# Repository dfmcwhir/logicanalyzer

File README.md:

# ISA Bus LogicAnalyzer

This is a fork of https://github.com/gusmanb/logicanalyzer. It utilizes that project's ability to chain multiple logic analyzers together with a chain of 3 of them them on a card that plugs into an 8 bit ISA bus slot. 47 of the channels are connected to A0-19, D0-7, and various other signals on the ISA bus. The 3rd logic analyzer goes to a header, so they can be jumpered over to other points on a motherboard (like buffer/latch/ram/rom CS or OE enable pins) as needed.

It is a work in progress. Circuit boards have been made and kicad and gerber files are in the electronics\ISA_Logic_analyzer folder. Assembly of the first board is in progress, so no testing has been done yet.

## About the project

This README is organized as a log of the evolution of the project and for now it will stay like this.
If you are new to the project and want to know what is this about you can start [here](https://github.com/gusmanb/logicanalyzer?tab=readme-ov-file#description)
or reading [the wiki](https://github.com/gusmanb/logicanalyzer/wiki).

Beware, the documentation is a bit outdated, I will try this summer to upgrade everything.

## Orders
- Direct order (based on availability): https://logicanalyzer.rf.gd (right now orders are not accepted)
- PCBWay order: https://www.pcbway.com/project/shareproject/LogicAnalyzer_V6_0_cc383781.html

## Enclosure
- @Bravo13 has created a pretty cool enclosure for V6.0, you can order it [here](https://www.pcbway.com/project/shareproject/Enclosure_for_LogicAnalyzer_V6_0_b82ed490.html)

## Downloads
- You can find all the compiled projects in the [Releases section](https://github.com/gusmanb/logicanalyzer/releases).
- Latest version: Release 6.0.0.1, 09/02/2025

# Beta 6.5 available

Wanna try the next version? Check [this discussion](https://github.com/gusmanb/logicanalyzer/discussions/277) :)

# ZX Spectrum analyzer by Happy Little Diodes!

If you are into retro computing and more specifically the ZX Spectrum, you should check this video by Happy Little Diodes.
He has developed an interface to connect LogicAnalyzer in a very cool way to the ZX Spectrum.

Don't miss it!

https://www.youtube.com/watch?v=IHbIW8pi4Vo

# Release 6.0 is out!

Finally Release 6.0 is completed and comes with many, many changes!

First, I have uploaded the project to PCBWay, I will still serve orders but as there is too much demand to keep up with it I also have uploaded it as a shared project, so you don't need to wait for me having stock.
The project is found here: https://www.pcbway.com/project/shareproject/LogicAnalyzer_V6_0_cc383781.html
It is right now under review so I expect it to be available in a couple of days.

Next, now the gerber files, BOMs and centroid are included in the release packages so you don't need to search inside the projects in case you want to order it from another manufacturer.

That's regarding logistics, now, a brief resume of the changes:

- Pico2 is supported, the new design solves the problems with the IO glitches.
- Total revamp of the analysis software, including speed up of the rendering, autodetection of the analyzers, and the biggest change, all the Sigrok protocol decoders are supported!
- New terminal capture application, no more long inhuman command lines, configure the capture using the terminal application and trigger the capture specifying the capture settings file! (use TerminalCapture --help for more info)
- New All-in-one package, both apps in a single zip if you want to use both!
- And many, maaaaany more changes.

Next weeks I will update the wiki with updated usage and functionalities, for now if you have doubts read the Discussion section related threads and of course if you need help feel free to open a new thread.

Have fun!

## Orders

If you are interested in buying a premade board now you can request to be added to the list in https://logicanalyzer.rf.gd/

## Orders and sponsor, what is this about?

Ok, now, the explanation. It is getting to the point of being unmanageable the amount of requests, so I have created a website to make it easier to track these, I don't want to forget anyone and doing the management manually I'm sure that in one moment or other I would forget someone...
Feel free to contact me if ytou find any problem or open a message in the discussion section.

And the sponsoring thing... I never requested anything for these projects, but lately many many people is asking about how to donate so finally I have opened a Ko-Fi account in order to accept them. Feel free to use it, anything is welcome and I will use it in improving the project whenever it is possible :)

Thanks to everyone, the support that I'm receiving with the project is amazing and I never thought that this project would rise so much interest.

### Thank you!

----

# Back!

Hi. I was in a business trip past weeks and got back today, so I have a ton of emails and messages regarding the project unanswered.

I will answer all the emails and requests this weekend/next Monday.

Sorry! :)

----

# Good news

One of the goals of the new design was to overcome the problems that the Pico 2 have. And at least, the most harmful one seems to be solved.
With the regular design the fast/complex trigger sometimes got stuck and the chaining didn't worked, with the new one the triggers seem work properly.

I need to conduct more tests as I have seen some response variations at high frequencies but I'm not sure if its caused by the pico2 itself or the transceivers as the analyzer is pushing them to its maximum limits.

I'm testing the devices with signals at 200Mhz, with the base pico all seems to work properly but with the pico2 I have seen changes on the signals, but, the TXU are rated up to 200Mhz and I'm sampling at 400Ms/s (yes, that's right, the new firmware can sample up to 400Ms/s in blast mode, I will add more info very soon as R6.0 is very close to its release 😄) so what I'm seeing is captures that have skewed samples. 
The signals that I use are basically square clocks, so I inject a 100Mhz clock what becomes two phases at 200Mhz, and with the pico2 at 400Ms/s I see that sometimes there are three samples of one phase and one sample of the other, and as far as I have seen is always the high phase the one that contains the three samples. This could be caused by the transceivers, they are at its maximum limits, but it can be also caused by the pico2, I suspect that even with the drainig of the GPIOs the signal remains high for some nanoseconds, enough to create these erroneous readings.

In any case, at least this only happens at extreme speeds and for regular use cases it should not affect the readings, and having three times more samples really expands the possibilities.

I will add more info next week after performing more extensive tests.

Stay tuned!

----

# New PCB design

I have created a new dessign for version 6.0 and is under testing right now.
It replaces the headers that were difficult to find, uses 0402 type components so is not intended for manual assembly and also include a VREF switch that allows to change between 3.3v/5v/ext vref.

Once testing is completed I will publish the dessign, I might have some spare  boards with all the components already assembled except for the pico, so if you are interested in one of these leave a message un the discussion sections (if I see that there is enough demand I might even think on making a batch of these).

----

# Pico 2: born dead.

Ok, this are bad news. The Pico 2 has been released in a basically useless status. It has been detected a bug in the GPIO hardware that locks the pins whenever you input a high level, what is known as "Errata E9".
According to the official errata the lock only happens when the pull downs are enabled, you input a high level value and then the GPIO starts outputing 2.1v. That doesn't sounds too bad but the reality is very different. I've been testing it and even forcing the pulldowns to be disabled, the PIO triggers the lock.
In this state, the RP2350 is useless if you need to use the GPIO's to input any data. The only workaround provided is to disable the pins and enable them when you are going to read and disable them after it to reset the pin status, but as you can imagine with the PIO this is impossible, and even if it was possible the capture speed would be reduced so much that the analyzer would be totally useless.

Unfortunatelly I must stop the port to the Pico 2 until this situation is solved.

# Pico 2: a game changer?

I've started checking the Pico 2 and porting the code to it. I must say that it has been one of the easiest transitions that I ever did, just reconfigure the cmake scripts, change a couple of lines, and voi-la! the project runs in the pico 2.

This is the base code, no changes at all, but from here I have multiple improvements to do, starting with the DMA (no mode ping-pong DMAs for the Pico 2, a single DMA can do all the work simplifying the code A LOT) and then upgrading the buffers to three times what are now, I expect to have up to 380k samples :)

Said that, I started checking the limits of the pico 2 and... well, I'm really surprised, with the original pico I only got stable up to 200Mhz, beyond that I had problems with the flash and it got hung, but, oh my gosh, this thing (the pico 2) right now is running at 400Mhz without a single hicup!!

Of course I had to raise the voltage to 1.4v for the core and it gets warmer, but I added a little heatsink to it and it's perfectly fine. Soooo.... I need to test this in deep but this may be a very, very big change, not only three times the samples than the pico, but also twice the speed!

Stay tuned for more news!

----

# Help wanted!

I'm cooking something very special, if you whant to know what it is and help with it, [check this post](https://github.com/gusmanb/logicanalyzer/discussions/127).
😉

# More boards on the go!

One of the new functionalities of the RP2350 is the capability of having two XIP devices and also has the full device implementation (RP2040 only had READ capabilities implemented). This means that is possible to have (for example) a flash device *and* a PSRAM connected to it.
Unfortunatelly the Pico 2 does not expose the QSPI pins and they are tied directly to the flash... But there is hope! PiMoroni has developed the PiMoroni Pico Plus 2 which contains 16Mb of flash and 8Mb of PSRAM.

I already have ordered one of these new boards and have some ideas on what could be done with them :D
Right now the most possible one is this: PSRAM is not fast enough for sampling at a decent speed with many channels, BUT, it is fast enough for something like storing ADC samples, so what I'm going to try is to allow the mix of analog and digital channels. The analog channels will be very slow compared to the digital ones (only 500Ks/s) but it still can be useful to monitor behaviors of things like motors, servos or whatever. As the PSRAM is 8Mb it will allow to store up to 8 seconds of analog data on single channel mode (2 bytes per sample at 500Ks/s is roughly 1Mb/s of data), this, combined with the upgraded onboard ram and the burst mode can be really useful in multiple projects.

Stay tuned for more news!

----

# Exciting news! The Pico 2 is coming soon!

As some of you may know the Pico 2 is being released this month. The new Pico 2 is a very exciting upgrade of the pico, more powerful cores, two alternative RiscV cores, three PIO units instead of two and 520Kb of RAM!

This can be a game changer for LogicAnalyzer, only with the new ammount of RAM the quantity of samples is going to increase massively, we're talking about three times the current ammount of samples!

Also, there are really exciting changes on the PIO side, the new IRQ system allows to intercomunicate the PIO units, this means that the trigger pins could be freed now, and this, as small change as it seems can be really amazing combined with the new third PIO unit... Think about this, a 64Mb dual SPI RAM running at 100Mhz connected to the two free pins and controlled at full speed by the third PIO unit... 

I was preparing a release for this month but it's going to be delayed, once I receive the new Pico's I will start the development for the Pico 2 and once it's completed I will release all at once.

Stay tuned!

## RELEASE 5.1

This release is a QoL release with some functional corrections. For more details check the release page.

## RELEASE 5.0, Burst mode is here!

New release with exciting feature!

The biggest change on this release is the Burst mode. With burst mode you can capture blocks of data and the analyzer will rearm itself immediatelly and capture more data when the trigger condition is met again. This will improve the memory usage discarding unneeded samples! Right now only the simple trigger mode accepts burst mode but in a future I will try to implement it in all the other triggers.
For more information check [the wiki.](https://github.com/gusmanb/logicanalyzer/wiki/06---The-LogicAnalyzer-program#triggers)

Also new features to ease the navigation in the capture viewer have been added like shortcuts and a preview of the full capture. More info in [the wiki.](https://github.com/gusmanb/logicanalyzer/wiki/06---The-LogicAnalyzer-program#navigating-on-the-capture-viewer)

Finally multiple improvements have been done, some bugs in the capture tail detection have been corrected, the USB transfer has been improved using directly the CDC transfer functions and more.

Beware that this version is not compatible with other ones, the protocol has changed. The driver will check the device version and will not connect to it if it is lower than V5.0.

Have fun!

----

## UPDATE 28/06/2023 - Release 4.5.1 - QOL improvements

This release include some QOL updates to the applications.

LogicAnalyzer app:

* Ammount of on-screen samples will be preserved if you repeat the last capture.
* Added a new menu entry called "Repeat las analysis" to the protocol analyzers, it will execute the last analysis performed to speed up things.
* Changed where config files are stored, they will use the %appData% folder now ($home/.config in Linux).
* Changed horizontal scrollbar visibility.

CLCapture app:

* Now channel names can be provided from the command line.

Have fun!

----

## UPDATE 11/04/2023 - Release 4.5 - Support for the RP2040-Zero and new board definition system

This release includes only an update to the firmware.

First, the RP2040-Zero is now officially supported (no shifter board for it though). 
You can download the firmware for it on the [releases](https://github.com/gusmanb/logicanalyzer/releases) section. Also, the pinout has been added to the [wiki](https://github.com/gusmanb/logicanalyzer/wiki/02---LogicAnalyzer-Hardware#barebones-configuration) so you can use it with the bare-bones configuration.

And second, the firmware has been refactored in order to make a lot easier to add new boards. You have the complete instructions on how to add support to a new board on [the wiki firmware section](https://github.com/gusmanb/logicanalyzer/wiki/03---LogicAnalyzer-Firmware). Also, as some boards include the very popular WS2812 RGB led the firmware includes a driver for it, it's purely software-based, no timers nor interrupts needed, so feel free to use it if you want.

If you add support for a new board, feel free to create a pull request with the changes :)

Have fun!

----

## UPDATE 25/02/2023 - Release 4.0 is up! Channels a go-go!

Hi again! This is a BIG update loaded with new functions and improvements to the hardware, firmware and software!

Let's start with the little things: we have a logo! Yes, it's nothing important but I hated to not to have a proper one so I designed one that I think fits well to the project :D

Next, we have a proper Wiki! All the project has been documented: hardware, firmware and software. If you have any doubt check it as I have tried to explain everything related to the analyzer usage in there. If you find any error or missing feature please open an issue and I will correct it as soon as I can.

Ok, now the changes to the hardware. There is a new pcb for the analyzer that includes two connectors to daisy chain the analyzers. You can use two or three Dupont wires (the central pin is unused, it's reserved for future usage, I have left it there so anyone that produces these PCB's can patch them easily).

And the firmware has also been updated to support the daisy chaining. So, what is for the daisy chaining? Well, daisy chaining allows to chain up to five analyzers without wasting pins so you now will be able to capture a massive ammount of **120 CHANNELS!!!** Check the [Connection](https://github.com/gusmanb/logicanalyzer/wiki/06---The-LogicAnalyzer-program#connecting-to-devices) and [Capture](https://github.com/gusmanb/logicanalyzer/wiki/06---The-LogicAnalyzer-program#capture) sections of the Wiki to know all the possibilities and how to use them.

Now, the software. It contains many changes, so I'm going to start with the improvements and then with the new functionalities.

First I have improved the sample rendering. It is now more visible and looks a lot better. Also, the guides shown to see where a sample starts and ends are automatically scaled or removed, it made no sense to have so many lines that they made a solid gray background, so when there are too many they will get automatically deactivated. Also, this allowed to improve the performance so now the sample viewer will allow to show up to 2000 samples in screen without any check.

Related to this the protocol analyzer renderer has been updated, it will take less useless space and will hide the information if it does not fit in the assigned space.

Now, the connection system has been updated to include a "multidevice", this is the device that you must use when using the daisy chained analyzers.

Next, the capture dialog has been updated, the mode selector has been removed and the mode is autoselected based in the channels enabled, check the [Wiki page](https://github.com/gusmanb/logicanalyzer/wiki/06---The-LogicAnalyzer-program#basic-parameters) to know the limits and modes.

Also, the capture dialog has a new channel selector, more visual and that includes the name field for the channels, instead of configuring the names after the capture has been finished (and lose these if you capture again) the names can be entered directly on the capture dialog. These names will be preserved between captures (and if you change them from the channel viewer these changes will be respected).

This new channel selector also allows to show up to the 120 channels that can be used when daisy chaining five devices, the selector will have a scrollbar when the channel list is bigger than its space.

Another change, the editing features have been improved and expanded. First of all, you will not need to create regions to execute edit actions, the sample range selection has been improved and it is used now for these. Check the [Wiki page](https://github.com/gusmanb/logicanalyzer/wiki/06---The-LogicAnalyzer-program#editing-captures) to see a description on how it works and which new features have been included.

Finally, the system now can create capture files from scratch, for this I have implemented a language that allows to describe signals in an easy way, it even includes a colored syntax editor, check the [Wiki](https://github.com/gusmanb/logicanalyzer/wiki/06---The-LogicAnalyzer-program#the-signal-description-language) for a description of this language!

Also, I already have planned the next update, I'm not sure when it will be ready but I will implement it for sure, and this is one of the motivations to create the SDL language: replay captures! ;)

This is a resume of the most prominent changes, surely that I forgot some, but all are documented in the Wiki, so ensure to review it!

Any feedback about the update will be welcome, so don't hesitate to open issues or start discussions.

Have fun!

## UPDATE 07/02/2023 - New release with updated shared driver.

This is a bug-fix release, with the introduction of the Pico-W WiFi support I unified the transfer mode in the driver using streams for network and for the serial port, but I forgot that .net 6.0 Ports package causes problems with Linux, so the previous release will hung the app when receiving more than 4k samples... Doh!

I have updated the code to use the same work around that I used previously and the problem has been fixed.

Have fun!

----

## UPDATE 04/02/2023 - New release! Bugs corrected and more samples!

Hi! This update comes loaded of news.

### First of all, bug corrections. 

The biggest bug that has been corrected is the fast trigger in the Pico-W. When I implemented the Pico-W I tried it extensively, but I used only the simple trigger to do the tests. What was my surprise when I tried to use the Pico-W with a fast trigger and I found that it got completely hung!

The thing is that the Pico-W hides a little secret that I haven't found documented anywhere, this little secret is that the driver uses a PIO program to do the transfers! The fast trigger uses a full PIO unit, all its 32 instructions to create a jump table, and the CYW driver uses a SM in the PIO1 to do the SPI transfers. So I tried to swap the PIO units and it at least started to capture, but the capture was never finished, I have revised up-to-down the driver and still haven't found why the PIO1 interrupts don't work at all after the CYW driver has been enabled, so I have done a work-around that does not need the IRQ to trigger a handler. So, if you are using a Pico-W update the firmware asap.

The next bug is a small bug that caused that some samples weren't clear correctly when a trigger was rised immediately after starting capture (for example the trigger condition is already met when the first sample is done).

### And now, the really big news, MORE SAMPLES!

I have tweaked the buffer transference between the PIO and the memory and it allows to hold up to 131071 samples! Of course this is at the expense of how many channels you use, the device now has three modes: 8 channels, 16 channels and 24 channels.

The sample limits are specified here:

 * Mode 8:
 
     * Minimum pre-samples: 2
     * Maximum pre-samples: 98303
     * Minimum post-samples: 512
     * Maximum post-samples: 131069
     * Maximum total samples: 131071
     
 * Mode 16:
 
     * Minimum pre-samples: 2
     * Maximum pre-samples: 49151
     * Minimum post-samples: 512
     * Maximum post-samples: 65533
     * Maximum total samples: 65535
     
 * Mode 24:
 
     * Minimum pre-samples: 2
     * Maximum pre-samples: 24576
     * Minimum post-samples: 512
     * Maximum post-samples: 32765
     * Maximum total samples: 32767

As you can see, using the 8 channel mode you can capture up to four times the samples that were available until now, a substantial increase.
The channels used for 8 and 16 modes must be the first ones, you cannot choose eight random channels, and this introduces a limitation, they collide with the complex and fast triggers (not the simple trigger, for that you still can use any channel left). Bear in mind this to plan how you configure your capture, for example for the 8 channel mode you still can have a 8 channel complex trigger or a fast 5 channel trigger without including these channels in the capture, but if you need more channels for one of these triggers, or you need to use the 16 channel mode you will suffer of this.

### Another new update, now you can show up to 1024 samples in screen!

You can activate this feature from the main screen, it has a checkbox (which will warn you as this may be a very CPU intensive task for old computers) that allows you to change the on-screen samples from 200 to 1024, this is really useful for use with big screens and modern computers.

Also I have tweaked a bit the appearance of the sample viewer, I didn't liked the dashed lines so now all are continuous ones.

Well, that's it for now.

Have fun!

----

## UPDATE 03/02/2023 - Measurement tool.

This is a very handy update to the analyzer, you can measure a region and get information of each channel: total samples selected, period of the selection, number of positive pulses, number of negative pulses, average and predominant period for positive and negative pulses and average and predominant frequency.

The predominant values are calculated applying a variant of the 95th percentile rule to discard aberrant/broken samples and I must say it works really well, it matched exactly all the frecuencies I have tested.

There is still no new release, you will need to compile the application if you want it, but I will create the release very soon.

Have fun!

----

## UPDATE 02/02/2023 - I2C protocol analyzer.

New day, new analyzer :D. This time is the turn for I2C. The analyzer will show you the raw data, the ACK/NACK's and will also show the device address (7 and 10 bit modes), operation of a request and any kind of frame error. To install it get it from [here](https://github.com/gusmanb/logicanalyzer/blob/master/I2CProtocolAnalyzer.dll) and copy it to the "analyzers" folder of the application.

Have fun!

----

## UPDATE 01/02/2023 - Serial protocol analyzer.

This is a small update, I have created a serial protocol analyzer (RS-232). This update does not include a release but I have left the analyzer library compiled in the repository. To install it get it from [here](https://github.com/gusmanb/logicanalyzer/blob/master/SerialProtocolAnalyzer.dll) and copy it to the "analyzers" folder of the application.

It supports positive and negative polarity (for TTL and RS-232 level signals), two channels (RX + TX), 7 or 8 bits, no parity/odd parity/even parity and 1, 1.5 or 2 stop bits.

Have fun!

----

## UPDATE 31/01/2023 - Pico-W support and WiFi!

It's finally here! WiFi support!

First of all, there are now three different firmware versions in the release section, one with no suffix for the regular pico, another with the "W" suffix for the Pico-W with no WiFi support and a final one with the "WIFI" suffix for the Pico-W with WiFi support. Choose the one that best suits your needs.

Now, how to use the WiFi support?

First of all, you need a Pico-W, I think that's obvious :D, flash it with the "WIFI" firmware and the device is ready to be used. If you plan to solder the Pico-W to the analyzer board beware to not to add the debug pins as they are now located in the middle of the board and it will not allow you to solder it, if you want them then you will need to use some pin headers to rise the Pico from the board (for my own device is what I always have done, in this way I can replace the Pico whenever I want).

Ok, now let's see how to use it.

First of all, you need to connect at least once the Pico-W to the computer to configure the network settings, this process can be done as many times as you want, connect the Pico-W to the computer and use the CLCapture or the LogicAnalyzer software to configure it.

When you connect the Pico-W with the WiFi firmware you will notice that a new menu gets enabled:

From there you can then select the "Update Network Settings" menu.

That will open the dialog to configure the network settings, you must enter the SSID of your router, the password (only WPA2 is supported), the desired static IP address and the listening TCP port.

Once these are configured accept them and they will be saved to the Pico-W flash, immediately the Pico-W will try to connect to your router, if it's available it will connect and it will be available for network connection.

To connect to the Pico-W through WiFi you must select from the dropdown menu the "Network" option.

Once you select it and press the "Open" button the network connection dialog will open.

Fill the IP address and port and press "Accept", if the device is available it will connect to it.

And that's it! From that point the device works exactly as before, for the application is indifferent if it is connected through network or USB, it has the exact same functionalities.

### The CLCapture updates

The CLCapture also supports the network connection and configuration, for that purpose now the command line starts with a verb, execute the program without any parameter to check the verbs and only with a verb to get the required parameters.

### Some notes

Both interfaces (USB and WiFi) work at the same time, but when a client gets connected through WiFi the USB will be ignored until the client gets disconnected, keep it in mind.

I have found some quirks on the Pico-W WiFi support, the first one is that it does not support at all to connect without a DHCP server, and it always gets the network information from there, fortunatelly I have found a way to change the IP address once it is connected to the AP. This also causes a problem (at least in my router), if you are already connected to the AP and you change the network settings the device disconnects from it and reconnects with the new info, if is the same AP (per example you have just changed the IP address) the static IP is ignored and it will retain the one assigned by the DHCP server, the solution is easy, restart the Pico-W and it will connect with the new IP address.

The firmware now has three "flavours" when compiled, this is controlled from the "LogicAnalyzer_Build_Settings.h" header and the "CMakeLists.txt" files, both contain instructions on how to change the settings based on your preferences.

A user adviced me that the Pico-W may have problems if the USB is connected to a host and the WiFi is used. I haven't experienced none of these and I have tested it extensively, maybe as I have used a sepparated core for the WiFi it avoids this kind of trouble, but if you experience them then use a USB power supply (like a phone charger or similar) if you want to connect through WiFi.

### The future

I'm thinking about creating a new PCB board that contains a battery and an USB charging module, in this way the device will become totally free of wires (except for the ones for the signals, obviously). I think this could be extremely useful, you will be able to place the analyzer even inside a computer or any kind of device and connect to it remotely, I think this could be extremely useful for devices that are in fixed places or are big and difficult to move (like old mini computers or car ECU's).

Stay tunned for more news, and be sure the project still is not completed!

Have fun!

----

## UPDATE 29/01/2023 - Software update

This release contains many updates to the GUI, CLI and driver and also includes many new target architectures.

### Updates to the GUI

First, the sample viewer and sample marker contains also the half of the cycle (where the sample was done in the cycle) to make it easier to see the data.

Now you can create a "user mark", it is a temporary mark and is not saved with the save/export data, just an useful tool to see things. Click on the sample marker without dragging and you will set the user mark place. To remove the user mark click again in the same spot.

Deleting samples is now possible, when you right-click on the sample marker over an existing region now instead of deleting the region it will pop a menu which will allow you to delete the regions that were under the mouse or to delete the regions *and* the samples.

Added more meaningful error messages, in any case the limits in the numeric up/down controls have been updated to match what the driver expects.

### Updates to the CLI

It also includes the new messages with more meaningful errors.

### Updates to the driver

The driver has been adjusted to give more flexibility in the pre/post samples, the valid parameters now are:

    -Frequency must be between 3.1Khz and 100Mhz
    -PreSamples must be between 2 and 31743
    -PostSamples must be between 512 and 32767
    -Total samples cannot exceed 32767
    
Have fun!

----

## UPDATE 17/12/2022 - Application repackaging

One of the features that I loved for .net when it was introduced is the ability to create applications that does not require the user to install the .net Framework independently. I always prefer to create portable packages, something that you uncompress wherever you want and it just works. This creates a bit bigger applications but nowadays with the massive storage devices we have and the fast Internet we have this is not a problem, while having to install the framework can be painful in some cases (restricted user privileges environments, problems with old .net installations, etc).

Well, thanks to the people at [Laboratoire Ouvert Grenoblois](https://www.logre.eu/) I found that the packages for unix/macos where incorrectly packaged and didn't included the framework and needed its installation... Doh!

I have re-packaged all the applications (CLI and GUI) and now all the versions include the required files, it should not need any more the installation of the .net framework.

Also, I have bumped up the firmware to the version that includes the new tail detection (beware, it will still inform that is the V1.0, I will correct the version numbering with the release of the Pico-W support).

Note: If you already have the applications and they are working ok for you that means that you already have the framework installed and there is no need to download the new packages, you only need these if you're doing a new installation or you had problems with the previous versions because the missing framework.

Have fun!

----

## UPDATE 12/12/2022 - Working towards Pico-W support

One of the goals that I want to achieve with the analyzer is to support the Pico-W. Would not be great to have a battery powered analyzer that connects to your computer via WiFi? For me at least this is a really desirable option as I have my main computer on a different desktop than the electronics bench, so when I want to analyze signals I must have a long USB cable hanging from the computer to the analyzer or I must do the analysis in the computer desktop. Also even if you are in the same desktop the less cables that you have around the easier is to work. For this, the Pico-W is ideal, as the analyzer does not transfer data in real time it does not need an extremely fast connection, for transferring the data once it has been captured the integrated WiFi of the Pico-W is more than enough.

### Pico-W missconceptions

It has been a while since I got the Pico-W and I didn't had enough time to start really digging on how the thing works, so my previous knowledge about the W was based on the first notes that were released to the Internet (I bought it at release day). Something that was stated in many places was that the W used some GPIO's to control the WiFi module so you would have less available IO's for your usage.

I have been really pleased when I have read by myself the datasheet and how the Pico has implemented in reality the WiFi module. It indeed uses some GPIO's to control the WiFi, but, those GPIO's have never been available to the user as regular GPIO's. The Pico uses GPIOs 23, 24, 25 and 29 for internal usage (LED, VBUS sense, etc). So, what have they done in the Pico-W to not to use additional GPIO's? They have lifted those functions to the GPIO's of the WiFi module. The WiFi module itself contains a GPIO port and now that port is the one that contains those functionalities, so now GPIO's 23, 24, 25 and 29 control the WiFi module and the first three GPIO's of the module are used for those functions.

So, what does all this means for the analyzer? Well, it means that very little changes needs to be done in the capture code and only the front-end code needs to be changed. Also, this means that the W version will also retain all the 24 channels, it will not lose any capability. Wohooo!!!

### Changes to the capture code

As all the GPIO's that are used to capture are the same there is no need to change any code except for one very small part, the "end capture" mark. The PIO always capture pins in a sequential way, it means that you cannot have "holes" in the pin sequence, and to get the full 24 channels every single available GPIO must be used, up to GPIO28. This means that the GPIOs that controlled the LED's, VBUS and so on also are captured but ignored. Said that, to mark where the capture was finished in the buffer a special value that was impossible to happen was added after the last capture, it was based on that the device those GPIOs would never be 1's. In theory, as we are capturing 32 bit words there will always be some zeroes at the tail, but I'm paranoid and also it is not elegant, so I decided to modify the tail detection code.

Instead of basing the tail detection in a mark in the buffer (which requires to iterate the buffer until it is found) now the tail detection is based in the DMA channels transfer state. This was my original idea, but unfortunatelly the Pico API does not expose a direct way of reading how many transfers have been done or how many are left, you can set them but cannot read them, so I abandoned that idea.

This time I have digged a bit more and went directly to the RP2040 datasheet and it states very clear that the TRANSFER register is R/W, so you can read how many transfers are left. I have no idea why the API does not expose it, but knowing that is very easy to access directly to the register using the dma hardware channel structure.

Now what the code does is: once the capture has finished before aborting the DMA channels it checks which one is busy (remember, there are four DMA channels in a ringed chain, so only one DMA will be busy, the one that's waiting for the next transfer from the PIO), checks how many transfers are left and based on the DMA channel number and the transfers left it computes the index of the last capture.

This is more elegant, faster and prevents that my paranoid side rings a bell each time I see that code thinking on the Pico-W, so all are advantages :D

### Wanna try it?

In the repo source under the [build](https://github.com/gusmanb/logicanalyzer/tree/master/Firmware/LogicAnalyzer/build) folder you will find the UF2 file with the new detection code, so you can try it with the Pico-W, it will still use the USB to transfer the data but you can check its compatibility. I still haven't got time to try it in the W but I plan to do it soon. In any case, if you test the new firmware in a W or a regular Pico I would be thankful if you can leave a comment telling your experience, if you have found any problem or if it worked as expected.

### Next steps

Well, the next step will be to add the front-end code for the W, the idea is to have a single project that based on settings compile it for the W or for the regular pico. About how to implement it, I still need to check the W API for the WiFi, but one thing that I want to do for sure is to have the WiFi module off when the capture is running to avoid any kind of glitch because interferences, I fear that the traces may act as antenna and read false data, so I'm thinking that I will use UDP instead of TCP, use a broadcast address to send/receive data and as UDP does not require an stablished connection it will allow to shut down the module without breaking the network. In any case these are my first thoughts and may change once I start implementing it.

Have fun as always!

----

## UPDATE 27/11/2022 - Small changes, great value

I have uploaded a new version of the PCB's and the firmware. It contains a small modification which can give great value to the device.
Do you have an oscilloscope? Have you ever wanted to trigger it based on the value of a data bus? Or when some digital signals take a concrete value?
Now the logic analyzer offers this functionality!

The modification is very simple, the GPIO pins used for the complex/fast triggers have been exposed through a diode and that signal can be used to trigger other devices like an oscilloscope. Or even you can chain multiple logic analyzers to have as many channels as you want! Configure your analyzer for a complex or fast trigger, connect your device to one of the EXT pins (and GND as needed) and start the capture. To chain multiple analyzers you must configure a simple trigger and connect one of the pins on the secondary analyzers to the EXT trigger pin. In the future and if it is requested I will add another capture mode for the EXT so it can chain more than 3 analyzers.

There is a small delay from the trigger to the signal, I have measured it and it is a delay of 20ns for the fast trigger (the two cycles that takes to detect and propagate the trigger condition) and 35ns for the complex one. Also, the diode introduces a small delay of 4ns, if you want to remove that delay you can skip the diode and the pull-down resistor and place a bridge where the diode should be placed, but be ware that you will leave the trigger unprotected against polarity inversions.

The external trigger has been routed to two pins, in this way you can chain as many analyzers as you want, or connect two other devices.

The new pinout is this:

Beware to not to use a new analyzer with an old shifter board, it has been also modified to include the ext signals, if you use an old sshifter with a new board you will create a short between +v5, +3.3v, GPIO0 and GPIO1 what will be fatal.

For the new shifter the pinout is the same as the analyzer but the +5v pin is the +5v/ext_ref depending on the jumper setting.

Finally I also have updated the firmware to disable the GPIO synchronizers what reduces other 4ns of delay.

Have fun!

----

## UPDATE 03/09/2022 - Abort captures
Minor release adding the capability to abort a running capture. To use this feature you will need to update the firmware and the application.

----
## UPDATE 27/08/2022 - LevelShifter update and more...

I have updated the level shifter board. It's a minor change but it makes the shifter a lot more flexible as now you can use the internal +5V as reference for the input voltages or you can use an external voltage source as reference. Basically this allows you to use the target device's voltage sources as VRef so the board now can work with levels between 1.65v and 5.5v

New board:

To use an external VRef source you need to remove the jumper JP1 and connect the external voltage reference to the +5v/ExtVRef pins of the input header.

BEWARE!!! There is no overvoltage protection for the VRef input so you must be careful to respect the 5.5v maximum voltage limit.

#### More things to come very soon:

- Capability to abort a running capture (under testing)
- Enclosure for the analyzer (a preview is already in the repository, do not use as I'm on the process of adjusting it)

Enjoy it!

----
## UPDATE 31/07/2022 - RELEASE 2.0

Good news! The multiplatform application is ready!

The application has been completely rewritten using AvaloniaUI, it works in Windows, Linux, Linux-ARM (Raspberry) and MacOSX.
It has been tested under Debian, Raspbian and Windows 10, MacOSX has not been tested as I don't have a working mac but it should work without problems.

Also, the new app includes improvements over the original one, like the ability to export the captures to Sigrok and better performance in general.

Application running in Windows:

Application running in Linux:

Application running in Raspberry:

----
## UPDATE 13/07/2022

I have managed to finally test the command line application in Linux and it worked as expected so I'm releasing it.

The command line capture program is a multiplatform command line application, it has versions for Linux, MacOSX and Windows and allows to capture data directly to a CSV file. The file format is compatible with Sigrok/PulseView so you can analyze the captures with it.

NOTE FOR LINUX/MACOSX USERS: Due to how I compile the apps you will need to make the app executable with CHMOD.

The app has been tested in Linux and Windows, if any user tests it on MacOSX please leave an issue with the results, I will be very thankful :D

### How to use the command line app:

If at any moment you need help you can execute `./CLCapture --help` and it will show you the usage help.

The app requires seven parameters to start a capture: serial port, sampling speed, channels to capture, pre-trigger samples, post-trigger samples, trigger definition and output file name.

- The first parameter is the name of the serial port of the logic analyzer.
- The second parameter is the desired capture speed in samples per second.
- The third parameter is a list of channels separated by coma, per example `1,2,3,4` or `1,16,24`.
- The fourth parameter is the number of samples to capture before the trigger.
- The fifth parameter is the number of samples to capture after the trigger.
- The sixth parameter is the trigger definition expressed in the form of: "TriggerType:(Edge, Fast or Complex),Channel:(base trigger channel),Value:(string - containing 1's and 0's indicating each trigger chanel state)". Per example, if we want an edge trigger on the positive edge using channel 4 the value would be `TriggerType:Edge,Channel:4,Value:1`. If we would want a fast trigger using channels 3,4,5 and a pattern of "101" the trigger definition would be `TriggerType:Fast,Channel:3,Value:101`. Note that there are no spaces, each parameter is separated by coma and no quote is used.
- Finally the seventh parameter is the output file name we want to generate.

A complete example to capture channels 1, 2, 3 and 4 at 100Mhz using channel 5 as positive edge trigger and storing the results in a file called "output.csv" would be similar to this:

```./CLCapture /dev/ttyACM0 100000000 1,2,3,4 512 1024 TriggerType:Edge,Channel:5,Value:1 output.csv```

If everything goes Ok you will see something like this:

```
Opening logic analyzer in port /dev/ttyACM0...
Conneced to device LOGIC_ANALYZER_V1_0 in port /dev/ttyACM0
Starting edge triggered capture...
Capture running...
```

The analyzer will blink while the capture is running and once it has finished it will print the result:
```
Capture complete, writting output file...
Done.
```

This capture will contain the data in CSV and is compatible with PulseView. To import it in PulseView go to "Open->Import comma-separated values...". The file is generated in a way that you don't need to change any of the CSV paramters, you will need to specify only the number of channels and the capture speed.

Once imported you will see your data, something like this:

I hope that with this, at least until the multiplatform app is ready, all the users can use the analyzer the way they want, it will work in all the common OS'es and it introduces compatibility with Sigrok/Pulseview in a way that is not intrusive for Sigrok nor for the LogicAnalyzer app.

Have fun!

----
## UPDATE 12/07/2022

I have received the shifter PCB's and there is an error. The footprints of J1 and J2 are exchanged, so what should be inputs are outputs and vice-versa. Thankfully this is not a problem, as the PCB is completely symmetric and it has components in both sides flipping the board fixes the problem.

Board before flip.

Board after flip.

The KiCad project is already updated.

The good news is that the board works like a charm, I have tested it with my clock generator with a 50Mhz clock and it captures every single half cycle perfectly, like if the board was not there :D

So if you want to build your own shifter board, it's ready and tested.

----
## Description
Cheap 24 channel logic analyzer with 100Msps, 32k samples deep, edge triggers and pattern triggers.

----
## Overview
LogicAnalyzer is a very cheap analyzer based in a Raspberry Pico. The analyzer offers up to 24 digital channels, pre and post trigger sampling, edge trigger and pattern trigger up to 16 bits.

The most basic version is purely a Pico as-is, you only need to short GPIO0 and GPIO1, upload the firmware and you're good to go.
Of course this has some limitations as the Pico only supports 3.3v, if you want to use it to diagnose 5v signals I also have designed a fast level shifter board.

Additionally to the hardware the logic analyzer also includes a powerful software (Windows only for now) where you can visualize the captured data, export captures, use protocol analyzers, etc.

## About logic analyzers and triggers

A logic analyzer only cares about logic states of lines, so without thinking much about it you may think that any microcontroller using DMA channels that read GPIO values would be more than enough, but that is the "easy" part of a logic analyzer, the problem comes when you need to trigger the captures based in GPIO states and you want also to have data captured previously and after the trigger happens.

For that, you need to compare the read values from the GPIOs check if the pin or pins values match the requested trigger and you must do it as fast as you want to capture, so for example, the most basic comparison will at least consume 3 or 4 instructions, if each instruction is 1 to 4 cycles (more or less, I'm thinking in ARM processors) then you will use up to 16 cycles to read a sample, so you would need a 1.6Ghz CPU to sample at 100Msps.

So, how the heck the pico is able to achieve this? Well, the key are the PIO units, these units are a wonder, they are coprocessors explicitly designed to handle IO, it uses a very restricted and deterministic assembler (only nine instructions that each take a single cycle to execute) but extremely efficient, so efficient that with only two instructions is possible to create a loop that captures GPIO data up to 30 bits and redirects the program flow based in the status of one of these GPIOs.

Of course there are some limitations, that two-instruction loop can only change the execution flow based on a GPIO pin, it can't branch based on a pattern (using only two instructions) but as we have more than one unit (each pico has two units and each unit has four state machines, so you can run in parallel up to 8 programs) we can abuse a bit the system and create a separate trigger program that notifies the capture program using a pin, that's why GPIO0 and GPIO1 are shorted.

The analyzer described here has three trigger modes: edge trigger, fast pattern trigger and complex pattern trigger.

The edge trigger uses a single program, that's the basic version that uses only two instructions, runs up to 100Msps and the triggering is synchronized with the captures.

The complex triggers is the first that uses two programs, one to capture and other for the trigger. The complex trigger supports patterns up to 16 bits matched from consecutive channels in the first 16 ones.
Having two programs is key to keep sampling up to 100Msps, the trigger program uses three instructions so its speed is limited to 66Msps, but the sampling can run at full speed using two instructions. Of course this presents some inconveniences, there is latency between the trigger signal and the reported trigger, also if the trigger pattern lasts less than one cycle at 66Mhz the trigger can be lost, and finally as the trigger always runs at maximum speed on lower speeds there may happen a "glitch", the trigger is raised because the pattern was found but the sampling program does not register this as it runs at a lower speed.

Finally we have the fast trigger, this uses a very clever "hack" (thanks to alastairpatrick from the Raspberry forums for the idea) that abuses the limitations of the PIO units. Each PIO unit can handle only 32 instructions, so the program counter of a state machine rolls to 0 if it's overflown, also the PIO assembler has an instruction to MOVe data from the IN pins to the program counter, and finally the PIO assembler allows to modify pin values on each instruction without using any extra cycle. So, said that, the trick consists on create a full 32 instruction program that moves the values from the GPIO to the PC and the instructions that are allocated in indexes that match the required pattern block the execution and sets a GPIO to 1.
Of course this limits the possibilities for the pattern, we can use up to 5 channels for this trigger but the trigger will run at full speed (it can work even faster, up to 200Msp).

If you want more info about the triggers check the PIO code in the source as there is more explanation on how this works.

## Schematic

The base schematic is only the Pico with a short between GPIO0 and GPIO1 but I have designed a PCB for convenience, it has been designed to maintain trace lengths so no glitch may happen because propagation delays (at 100Mhz it should not be a problem, but in marginal cases if there is a noticeable trace length difference some picoseconds of delay can be introduced and change the analyzed values).

Also, as the Pico only supports 3.3v I have designed a level shifter board, it uses very fast transceivers (TXU0104) which met the 100Msps specifications.

ATTENTION! I'm in the process of receiving the PCBs so they are not tested, I will update this document after testing it.

## PCB

There are two PCBs, one for the analyzer and other for the level shifter.

## Building the firmware

To build the firmware you need to have an environment configured for Pico development, but if you don't have it don't worry, the releases include the UF2 file, so you only need to start the Pico in program mode, drop the UF2 file to the Pico drive and that's it, you have a Logic Analyzer ready to be used.

## The software

Before designing my own analyzer I have used some cheap Chinese analyzers and all use the same software, OLS, OpenBench Logic Analyzer, and to be honest, I don't like it. So, I have implemented my own binary protocol (more info in the firmware code) and visualization software. 

This is a .net desktop program for Windows (if I have enough requests I may plan to create a .net MAUI version that runs in Windows/MacOS/Linux) which allows you to visualize the capture data, highlight sampling ranges, name channels extremely fast, export the captured data preserving the capture settings and ranges, implements protocol analyzers (and a very easy system to include your own ones) and so on.

For now I have already implemented a SPI protocol analyzer but I plan to implement also I2C, RS-232 and system bus analyzers (for old computers, 16 address bits and 8 data bits). In any case, with little knowledge of C# you can add your own protocol, which makes the program capable of analyze proprietary protocols.

The capture interface is straight and self-explanatory, and the software preserves your last settings, can import settings from exported captures and allows you to re-issue a capture without having to go through the configuration process.

## Build requirements

To build the firmware you will need a build environment for the Pico-SDK version 1.3.1 or newer. For Windows users I recommend to use the [Pico-Setup project](https://github.com/ndabas/pico-setup-windows/releases).

To build the application you will need [Visual Studio 2022](https://visualstudio.microsoft.com/) with the C# language installed.

## Using the device

The device once connected to your PC will be detected as a serial port, no drivers are needed. Once you open the software you will have a list of serial ports and you must choose the correct one, once selected if you "Open" the device it will show the firmware version in the top section and will enable the capture buttons.

To use the analyzer connect the required channels to the signals you want to analyze, also connect at least one ground pin from the Pico to the analyzed device, press the "Capture" button, configure your settings and start the capture. The Pico will start flashing until the trigger condition is met and the capture will run.

Once the capture has finished you will see the channels, a range of up to 100 samples and the trigger event will be right at the left side of the sample area.

To name your channels you have a grey box under each one, these are textboxes where you can set whatever you want, and if you export your capture they will be preserved.

To create an highlighted region press over the numeric top bar and drag to select how many samples are highlighted.

This will open the region creation dialog where you can choose a name for your region, the color and the opacity of the highlight.

If you want to delete a region press on the numeric bar over a highlighted region and it will be deleted. Regions are also exported with captures.

## Adding custom protocol analyzers

To add a new protocol analyzer you need to create a .net 6.0 assembly that references the LogicAnalyzer assembly and implements at least one class based in "ProtocolAnalyzerBase". Basically you will provide a list of settings to present to the user and then you will implement an analysis function that returns analyzed channels.

Each analyzed channel will specify a list of segments where data is overlayed (to present data to the user) and also it may provide a custom renderer for the data segments. You can create your own custom renderers or just provide an instance of the already included "SimpleSegmentRenderer".

---

## About Sigrok and the custom app

I have been reading some comments about why create my own application and why not use Sigrok as it would have been developed faster. First of all, the full project including firmware, PCB's and Windows client took me less than a week of development, I have been creating Windows apps for more than 20 years and it takes me less time to implement a rendering system, plugins and so on than implementing a third-party driver :)
In any case, my main reason to not consider to use sigrok is because I tried to use it with some cheapo analyzers and on my machines it simply would not run, I'm not sure if some component that I use for development is incompatible with it but on my three machines it crashed, in one machine it does not open at all and on the other two I had random crashes when I tried to capture data.

In any case, I will try to get it running in one of my development machines and if it works I will check how complex would be to create a driver for it.

---

Have fun!

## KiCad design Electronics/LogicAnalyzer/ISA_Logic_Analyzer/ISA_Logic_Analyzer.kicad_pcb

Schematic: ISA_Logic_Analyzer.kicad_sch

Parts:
C1, C2, C3, C4, C5, C6, C7, C8, C9, C10, C11, C12, C13, C14, C15, C16, C17, C18, C19, C20, C21, C22, C23, C24, C25, C26, C27, C28, C29, C30, C31, C32, C33, C34, C35, C36: 100n; C_0603_1608Metric_Pad1.08x0.95mm_HandSolder; MPN 0402X104M160CT
D1: 1N914; D_DO-41_SOD81_P10.16mm_Horizontal; MPN LL4148
D2: 1N4001; D_DO-41_SOD81_P10.16mm_Horizontal
J1: EXT_TRIG; PinHeader_1x02_P2.54mm_Vertical
J2: Bus_ISA_8bit; BUS_8-bit_ISA
J3: EXT_CHAIN; PinHeader_1x02_P2.54mm_Vertical
J4: Ext. Channels; PinHeader_2x16_P2.54mm_Vertical
J5: VREF_PICO_PWR_EN; PinHeader_1x02_P2.54mm_Vertical
R1: 100K; R_Axial_DIN0207_L6.3mm_D2.5mm_P7.62mm_Horizontal; MPN CRCW0402100KFKEE
R2, R3, R4: 8K2; R_Axial_DIN0207_L6.3mm_D2.5mm_P7.62mm_Horizontal; MPN CR0402AJW-822GLF
U1, U8, U15: TXU0104PWR; TSSOP_14_L5_0_W4_4_P0_65_LS6_4_BL_5; MPN TXU0104PWR
U2, U5, U19: TXU0104PWR; TSSOP_14_L5_0_W4_4_P0_65_LS6_4_BL_1; MPN TXU0104PWR
U3, U6, U20: TXU0104PWR; TSSOP_14_L5_0_W4_4_P0_65_LS6_4_BL_2; MPN TXU0104PWR
U4, U11, U18: TXU0104PWR; TSSOP_14_L5_0_W4_4_P0_65_LS6_4_BL_3; MPN TXU0104PWR
U7, U9, U16: TXU0104PWR; TSSOP_14_L5_0_W4_4_P0_65_LS6_4_BL_4; MPN TXU0104PWR
U10, U12, U17: TXU0104PWR; TSSOP_14_L5_0_W4_4_P0_65_LS6_4_BL; MPN TXU0104PWR
U13, U14, U21: PICO; COMM_SMD_L51_0_W21_0_P2_54_SC0916; MPN PICO

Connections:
/A0: J2.62 (BA00), U6.2 (A1)
/A0_OUT: U6.13 (B1Y), U14.15 (GP11)
/A1: J2.61 (BA01), U6.3 (A2)
/A1_OUT: U6.12 (B2Y), U14.14 (GP10)
/A2: J2.60 (BA02), U6.4 (A3)
/A2_OUT: U6.11 (B3Y), U14.12 (GP9)
/A3: J2.59 (BA03), U6.5 (A4)
/A3_OUT: U6.10 (B4Y), U14.11 (GP8)
/A4: J2.58 (BA04), U5.2 (A1)
/A4_OUT: U5.13 (B1Y), U14.10 (GP7)
/A5: J2.57 (BA05), U5.3 (A2)
/A5_OUT: U5.12 (B2Y), U14.9 (GP6)
/A6: J2.56 (BA06), U5.4 (A3)
/A6_OUT: U5.11 (B3Y), U14.7 (GP5)
/A7: J2.55 (BA07), U5.5 (A4)
/A7_OUT: U5.10 (B4Y), U14.6 (GP4)
/A8: J2.54 (BA08), U4.2 (A1)
/A8_OUT: U4.13 (B1Y), U14.31 (GP26)
/A9: J2.53 (BA09), U4.3 (A2)
/A9_OUT: U4.12 (B2Y), U14.29 (GP22)
/A10: J2.52 (BA10), U4.4 (A3)
/A10_OUT: U4.11 (B3Y), U14.27 (GP21)
/A11: J2.51 (BA11), U4.5 (A4)
/A11_OUT: U4.10 (B4Y), U14.26 (GP20)
/A12: J2.50 (BA12), U12.2 (A1)
/A12_OUT: U12.13 (B1Y), U14.25 (GP19)
/A13: J2.49 (BA13), U12.3 (A2)
/A13_OUT: U12.12 (B2Y), U14.24 (GP18)
/A14: J2.48 (BA14), U12.4 (A3)
/A14_OUT: U12.11 (B3Y), U14.22 (GP17)
/A15: J2.47 (BA15), U12.5 (A4)
/A15_OUT: U12.10 (B4Y), U14.21 (GP16)
/A16: J2.46 (BA16), U7.2 (A1)
/A16_OUT: U7.13 (B1Y), U13.15 (GP11)
/A17: J2.45 (BA17), U7.3 (A2)
/A17_OUT: U7.12 (B2Y), U13.14 (GP10)
/A18: J2.44 (BA18), U7.4 (A3)
/A18_OUT: U7.11 (B3Y), U13.12 (GP9)
/A19: J2.43 (BA19), U7.5 (A4)
/A19_OUT: U7.10 (B4Y), U13.11 (GP8)
/AEN: J2.42 (AEN), U1.2 (A1)
/AEN_OUT: U1.13 (B1Y), U13.10 (GP7)
/ALE: J2.28 (ALE), U8.3 (A2)
/ALE_OUT: U8.12 (B2Y), U14.19 (GP14)
/CLK: J2.20 (CLK), U10.2 (A1)
/CLK_OUT: U10.13 (B1Y), U13.20 (GP15)
/D0: J2.40 (DB0), U1.4 (A3)
/D0_OUT: U1.11 (B3Y), U13.7 (GP5)
/D1: J2.39 (DB1), U1.5 (A4)
/D1_OUT: U1.10 (B4Y), U13.6 (GP4)
/D2: J2.38 (DB2), U3.2 (A1)
/D2_OUT: U3.13 (B1Y), U13.29 (GP22)
/D3: J2.37 (DB3), U3.3 (A2)
/D3_OUT: U3.12 (B2Y), U13.27 (GP21)
/D4: J2.36 (DB4), U3.4 (A3)
/D4_OUT: U3.11 (B3Y), U13.26 (GP20)
/D5: J2.35 (DB5), U3.5 (A4)
/D5_OUT: U3.10 (B4Y), U13.25 (GP19)
/D6: J2.34 (DB6), U2.2 (A1)
/D6_OUT: U2.13 (B1Y), U13.24 (GP18)
/D7: J2.33 (DB7), U2.3 (A2)
/D7_OUT: U2.12 (B2Y), U13.22 (GP17)
/DRQ1: J2.18 (DRQ1), U10.3 (A2)
/DRQ1_OUT: U10.12 (B2Y), U13.19 (GP14)
/EXT_CHAIN: D1.2 (A), J3.1, R2.1, R3.1, R4.1, U13.1 (GP0), U13.2 (GP1), U14.1 (GP0), U14.2 (GP1), U21.1 (GP0), U21.2 (GP1)
/EXT_TRIG: D1.1 (C), J1.1, R1.1
/GND: C1.1, C2.1, C3.1, C4.1, C5.1, C6.1, C7.1, C8.1, C9.1, C10.1, C11.1, C12.1, C13.1, C14.1, C15.1, C16.1, C17.1, C18.1, C19.1, C20.1, C21.1, C22.1, C23.1, C24.1, C25.1, C26.1, C27.1, C28.1, C29.1, C30.1, C31.1, C32.1, C33.1, C34.1, C35.1, C36.1, J1.2, J2.1 (GND), J2.10 (GND), J2.31 (GND), J3.2, J4.6, J4.8, J4.30, J4.32, R1.2, R2.2, R3.2, R4.2, U1.7 (GND), U2.7 (GND), U3.7 (GND), U4.7 (GND), U5.7 (GND), U6.7 (GND), U7.7 (GND), U8.7 (GND), U9.7 (GND), U10.7 (GND), U11.7 (GND), U12.7 (GND), U13.3 (GND0), U13.8 (GND1), U13.13 (GND2), U13.18 (GND3), U13.23 (GND4), U13.28 (GND5), U13.33 (GND6), U13.38 (GND7), U14.3 (GND0), U14.8 (GND1), U14.13 (GND2), U14.18 (GND3), U14.23 (GND4), U14.28 (GND5), U14.33 (GND6), U14.38 (GND7), U15.7 (GND), U16.7 (GND), U17.7 (GND), U18.7 (GND), U19.7 (GND), U20.7 (GND), U21.3 (GND0), U21.8 (GND1), U21.13 (GND2), U21.18 (GND3), U21.23 (GND4), U21.28 (GND5), U21.33 (GND6), U21.38 (GND7)
/IO: J2.32 (IO), U2.4 (A3)
/IOR: J2.14 (~IOR), U10.4 (A3)
/IOR_OUT: U10.11 (B3Y), U13.17 (GP13)
/IOW: J2.13 (~IOW), U10.5 (A4)
/IOW_OUT: U10.10 (B4Y), U13.16 (GP12)
/IO_OUT: U2.11 (B3Y), U13.21 (GP16)
/IO_READY: J2.41 (IO_READY), U1.3 (A2)
/IO_READY_OUT: U1.12 (B2Y), U13.9 (GP6)
/IRQ2: J2.4 (IRQ2), U11.4 (A3)
/IRQ2_OUT: U11.11 (B3Y), U13.32 (GP27)
/IRQ3: J2.25 (IRQ3), U8.5 (A4)
/IRQ3_OUT: U8.10 (B4Y), U14.16 (GP12)
/IRQ4: J2.24 (IRQ4), U9.2 (A1)
/IRQ4_OUT: U9.13 (B1Y), U14.5 (GP3)
/IRQ5: J2.23 (IRQ5), U9.3 (A2)
/IRQ5_OUT: U9.12 (B2Y), U14.4 (GP2)
/IRQ6: J2.22 (IRQ6), U9.4 (A3)
/IRQ6_OUT: U9.11 (B3Y), U14.34 (GP28)
/IRQ7: J2.21 (IRQ7), U9.5 (A4)
/IRQ7_OUT: U9.10 (B4Y), U14.32 (GP27)
/MEMR: J2.12 (~SMEMR), U11.2 (A1)
/MEMR_OUT: U11.13 (B1Y), U13.5 (GP3)
/MEMW: J2.11 (~SMEMW), U11.3 (A2)
/MEMW_OUT: U11.12 (B2Y), U13.34 (GP28)
/OSC: J2.30 (OSC), U8.2 (A1)
/OSC_OUT: U8.13 (B1Y), U14.20 (GP15)
/POWER_3v3_A: C26.2, C28.2, C30.2, C32.2, C34.2, C36.2, U15.8 (OE), U15.14 (VCCB), U16.8 (OE), U16.14 (VCCB), U17.8 (OE), U17.14 (VCCB), U18.8 (OE), U18.14 (VCCB), U19.8 (OE), U19.14 (VCCB), U20.8 (OE), U20.14 (VCCB), U21.36 (P_3V3_OUT)
/POWER_3v3_B: C14.2, C16.2, C18.2, C20.2, C22.2, C24.2, U4.8 (OE), U4.14 (VCCB), U5.8 (OE), U5.14 (VCCB), U6.8 (OE), U6.14 (VCCB), U8.8 (OE), U8.14 (VCCB), U9.8 (OE), U9.14 (VCCB), U12.8 (OE), U12.14 (VCCB), U14.36 (P_3V3_OUT)
/POWER_3v3_C: C7.2, C8.2, C9.2, C10.2, C11.2, C12.2, U1.8 (OE), U1.14 (VCCB), U2.8 (OE), U2.14 (VCCB), U3.8 (OE), U3.14 (VCCB), U7.8 (OE), U7.14 (VCCB), U10.8 (OE), U10.14 (VCCB), U11.8 (OE), U11.14 (VCCB), U13.36 (P_3V3_OUT)
/Pico_PWR: D2.1 (K), U13.39 (VSYS), U14.39 (VSYS), U21.39 (VSYS)
/RESET: J2.2 (RESET), U11.5 (A4)
/RESET_OUT: U11.10 (B4Y), U13.31 (GP26)
/SP1: J4.31, U20.2 (A1)
/SP1_OUT: U20.13 (B1Y), U21.4 (GP2)
/SP2: J4.29, U20.3 (A2)
/SP2_OUT: U20.12 (B2Y), U21.5 (GP3)
/SP3: J4.27, U20.4 (A3)
/SP3_OUT: U20.11 (B3Y), U21.6 (GP4)
/SP4: J4.25, U20.5 (A4)
/SP4_OUT: U20.10 (B4Y), U21.7 (GP5)
/SP5: J4.23, U19.2 (A1)
/SP5_OUT: U19.13 (B1Y), U21.9 (GP6)
/SP6: J4.21, U19.3 (A2)
/SP6_OUT: U19.12 (B2Y), U21.10 (GP7)
/SP7: J4.19, U19.4 (A3)
/SP7_OUT: U19.11 (B3Y), U21.11 (GP8)
/SP8: J4.17, U19.5 (A4)
/SP8_OUT: U19.10 (B4Y), U21.12 (GP9)
/SP9: J4.15, U18.2 (A1)
/SP9_OUT: U18.13 (B1Y), U21.14 (GP10)
/SP10: J4.13, U18.3 (A2)
/SP10_OUT: U18.12 (B2Y), U21.15 (GP11)
/SP11: J4.11, U18.4 (A3)
/SP11_OUT: U18.11 (B3Y), U21.16 (GP12)
/SP12: J4.9, U18.5 (A4)
/SP12_OUT: U18.10 (B4Y), U21.17 (GP13)
/SP13: J4.7, U17.2 (A1)
/SP13_OUT: U17.13 (B1Y), U21.19 (GP14)
/SP14: J4.5, U17.3 (A2)
/SP14_OUT: U17.12 (B2Y), U21.20 (GP15)
/SP15: J4.3, U17.4 (A3)
/SP15_OUT: U17.11 (B3Y), U21.34 (GP28)
/SP16: J4.1, U17.5 (A4)
/SP16_OUT: U17.10 (B4Y), U21.32 (GP27)
/SP17: J4.24, U16.2 (A1)
/SP17_OUT: U16.13 (B1Y), U21.31 (GP26)
/SP18: J4.22, U16.3 (A2)
/SP18_OUT: U16.12 (B2Y), U21.29 (GP22)
/SP19: J4.20, U16.4 (A3)
/SP19_OUT: U16.11 (B3Y), U21.27 (GP21)
/SP20: J4.18, U16.5 (A4)
/SP20_OUT: U16.10 (B4Y), U21.26 (GP20)
/SP21: J4.16, U15.2 (A1)
/SP21_OUT: U15.13 (B1Y), U21.25 (GP19)
/SP22: J4.14, U15.3 (A2)
/SP22_OUT: U15.12 (B2Y), U21.24 (GP18)
/SP23: J4.12, U15.4 (A3)
/SP23_OUT: U15.11 (B3Y), U21.22 (GP17)
/SP24: J4.10, U15.5 (A4)
/SP24_OUT: U15.10 (B4Y), U21.21 (GP16)
/TC: J2.27 (TC), U8.4 (A3)
/TC_OUT: U8.11 (B3Y), U14.17 (GP13)
/VREF: C1.2, C2.2, C3.2, C4.2, C5.2, C6.2, C13.2, C15.2, C17.2, C19.2, C21.2, C23.2, C25.2, C27.2, C29.2, C31.2, C33.2, C35.2, J2.3 (VCC), J2.29 (VCC), J4.2, J4.4, J4.26, J4.28, J5.1, U1.1 (VCCA), U2.1 (VCCA), U3.1 (VCCA), U4.1 (VCCA), U5.1 (VCCA), U6.1 (VCCA), U7.1 (VCCA), U8.1 (VCCA), U9.1 (VCCA), U10.1 (VCCA), U11.1 (VCCA), U12.1 (VCCA), U15.1 (VCCA), U16.1 (VCCA), U17.1 (VCCA), U18.1 (VCCA), U19.1 (VCCA), U20.1 (VCCA)
unnamed: D2.2 (A), J5.2

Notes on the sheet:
Back Side Analyzer
Front Side Analyzer
Spare Analyzer

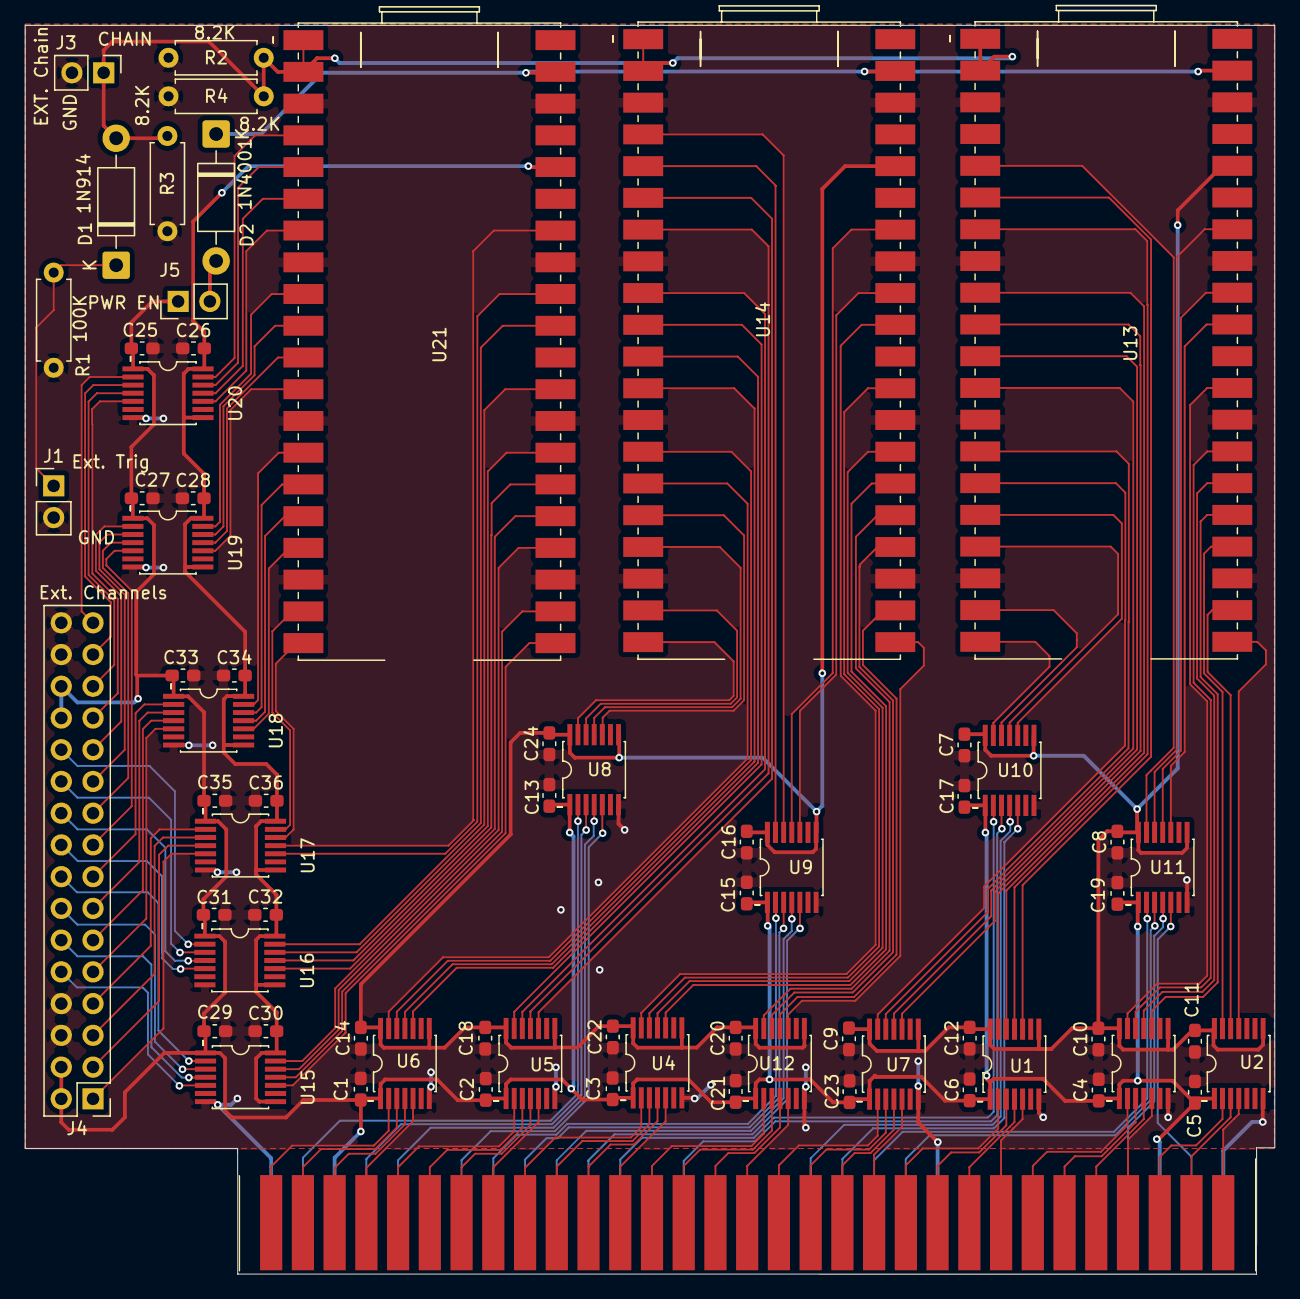
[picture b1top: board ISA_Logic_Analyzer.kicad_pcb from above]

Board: 2 copper layers, 100.0 x 100.0 mm, 68 parts (0 on the bottom side), 151 nets.

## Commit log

2026-05-28 Change 'Hello World' to 'Goodbye World'
2026-05-28 Change greeting from 'Hello' to 'Goodbye'
